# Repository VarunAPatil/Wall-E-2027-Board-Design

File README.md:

# Wall-E SRA Board · 2026–27

**A KiCad hardware platform for the Society of Robotics and Automation (SRA), VJTI.**

The SRA board brings the control, sensing, display, power, and motor interfaces for a small mobile robot onto one development board. This repository contains the main SRA board design, its companion Line Sensor Array (LSA), local KiCad libraries, 3D models, and fabrication exports.

---

## At a glance

| Area | Design |
| --- | --- |
| Main controller | ESP32-S3-WROOM-1 module |
| Input and power | 12 V input, TPS54302 step-down stage, 5 V rail, AMS1117-3.3 V regulator |
| Motor control | TB6612FNG dual H-bridge and two motor outputs |
| Robot sensing | 10-pin FFC connection for the LSA; MPU-6050 connection |
| User interface | OLED connection, MAX7219-driven 8×8 LED matrix, buttons and status signals |
| Host connection | USB-C USB 2.0 interface for development and programming |
| Design tools | KiCad schematic, PCB, project and local symbol/footprint libraries |

> **Design status:** This repository contains design files and exported fabrication data. Their presence does not by itself confirm electrical validation, manufacturing quality, or tested board behavior. Check the current schematic, PCB, and fabrication outputs before ordering or assembling hardware.

## System overview

```mermaid
flowchart LR
    P[12 V input] --> PR[Input protection and switching]
    PR --> B[TPS54302 buck stage]
    B --> V5[5 V rail]
    V5 --> L[AMS1117-3.3 V regulator]
    V5 --> M[TB6612FNG motor driver]
    L --> C[ESP32-S3]
    C <--> U[USB-C USB 2.0]
    C <--> D[MAX7219 LED matrix]
    C <--> O[OLED]
    C <--> I[MPU-6050]
    C <--> A[10-pin FFC to LSA]
    M --> W[Left and right motor outputs]
```

The power design separates the motor supply from the regulated logic rails. The schematic shows a TPS54302 switching regulator for the 5 V rail and an AMS1117-3.3 for 3.3 V logic. Resettable PTC fuses are used in the design; the schematic lists 3 A and 1 A parts. These values describe the selected components, not a verified continuous-current rating for a completed board.

The main controller connects to the motor driver and the board peripherals. The TB6612FNG provides two H-bridge channels for two DC motor outputs. The MAX7219 handles the LED matrix interface, reducing the number of controller signals needed for the display. The OLED and MPU-6050 connect as board peripherals, and the companion LSA connects over the 10-pin FFC interface.

## Board features

### SRA controller board

- **ESP32-S3 control:** Wi-Fi/Bluetooth-capable MCU module and GPIO-based control for the robot and its peripherals.
- **USB-C interface:** USB 2.0 data connection to the controller for development and programming.
- **12 V power path:** board input with switching and protection circuitry, followed by regulated 5 V and 3.3 V rails.
- **Dual motor driver:** TB6612FNG H-bridge with separate control signals and two motor connectors.
- **Line sensing:** 10-position, 1.0 mm pitch FFC connector to the companion LSA board.
- **Motion sensing:** connection for an MPU-6050 inertial measurement module.
- **Display and feedback:** OLED connection and an 8×8 LED matrix driven by a MAX7219.
- **Controls:** reset/boot buttons and board-level power control signals.

### Line Sensor Array (LSA)

The `lsa/` directory contains a separate KiCad project for the line sensor board. It connects to the SRA board through a 10-pin FFC cable. Its schematic includes five analog sensor outputs labelled `LSA_A0` through `LSA_A4`; use the schematic and board pin labels as the wiring reference when integrating it.

## Repository map

| Path | Contents |
| --- | --- |
| `sra_board.kicad_pro` | Main SRA KiCad project settings |
| `sra_board.kicad_sch` | Main board schematic |
| `sra_board.kicad_pcb` | Main board PCB layout |
| `sra_board.step` | 3D STEP export of the main board assembly |
| `lsa/lsa.kicad_pro` | LSA KiCad project settings |
| `lsa/lsa.kicad_sch` | LSA schematic |
| `lsa/lsa.kicad_pcb` | LSA PCB layout |
| `3D/` | Component STEP models used by the designs |
| `MAX7219/` | MAX7219 symbol, footprints, and supporting files |
| `footprints.pretty/` | Project-specific KiCad footprints |
| `fp-lib-table`, `sym-lib-table` | Project-local footprint and symbol library tables |
| `sra-board-final-iteration-2027/` | Gerber, drill, and job files for the SRA board |
| `lsa/LSA-Wall-E-2027/` | Gerber, drill, and job files for the LSA board |
| `assets/` | Reference board images from an earlier board snapshot; compare with the current PCB before relying on them |

## Open and work with the designs

1. Install KiCad and clone this repository with Git, or download the repository as a ZIP archive.
2. Open `sra_board.kicad_pro` in KiCad to work on the SRA board. Open `lsa/lsa.kicad_pro` for the LSA.
3. Keep the project files, library tables, local footprints, symbols, and 3D models together so KiCad can resolve the project-specific references.
4. Make schematic changes first, then update the PCB from the schematic in KiCad and review footprints, net assignments, clearances, and board geometry.
5. Re-export fabrication files from the reviewed PCB if it has changed. The checked-in Gerbers are snapshots and may not match later edits.

### Fabrication files

The two export directories contain copper, solder-mask, solder-paste, silkscreen, outline, drill, and Gerber job files. Use the matching directory for the board being fabricated. Before sending files to a manufacturer, confirm that the exports correspond to the intended revision and inspect the layer set, board outline, drill map, and fabrication notes in a Gerber viewer.

The `.step` files are for mechanical and enclosure review. They are not substitutes for the KiCad source files or fabrication exports.

## Power and battery notes

The board is designed around a 12 V input for the motor and board power path. If using a three-cell lithium-ion battery pack, use a correctly rated external 3S battery-management system (BMS) and charger. The BMS is not the board’s battery charger. Confirm the voltage range, polarity, connector pinout, fuse suitability, motor current, regulator thermal limits, and wiring before powering a completed assembly.

## Project context and contributors

The SRA board is used in SRA VJTI robotics work, including the [Wall-E](https://github.com/SRA-VJTI/Wall-E) and [MARIO](https://github.com/SRA-VJTI/MARIO) projects. The board is designed in KiCad.

- [Varun Patil](https://github.com/VarunAPatil) — Designer
- [Omkar Nanajkar](https://github.com/nomkar24) — Designer

## License

There is no `LICENSE` file in this repository at present. Check with the project maintainers before reusing or redistributing the hardware design.

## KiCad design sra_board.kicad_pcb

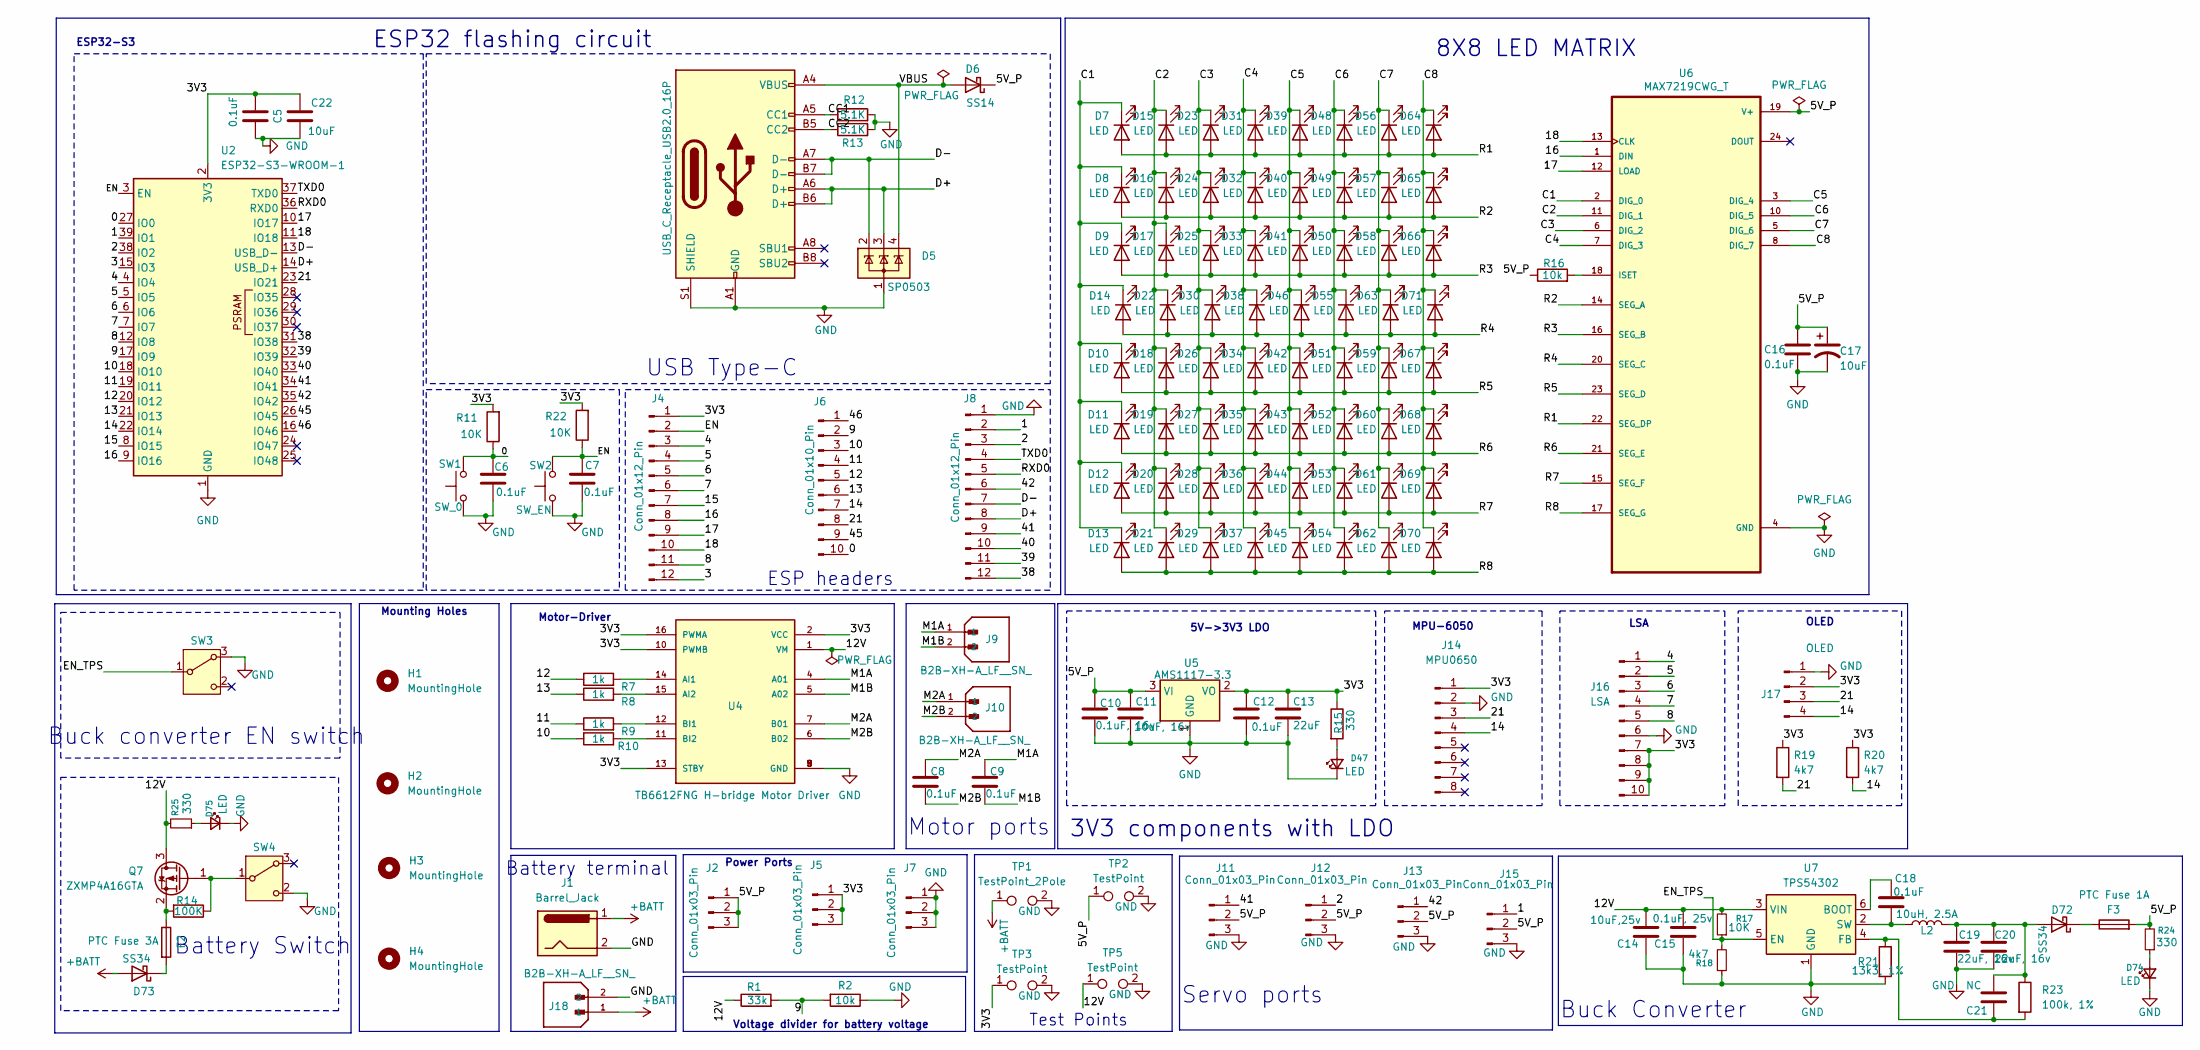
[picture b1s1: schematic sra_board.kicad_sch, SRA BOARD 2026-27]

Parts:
C5, C6, C7, C12, C16, C18: 0.1uF; C_0805_2012Metric
C8, C9: 0.1uF; C_1206_3216Metric
C10: 0.1uF, 16v; C_0805_2012Metric
C11: 10uF, 16v; C_0805_2012Metric
C13: 22uF; C_0805_2012Metric
C14: 10uF,25v; C_1206_3216Metric
C15: 0.1uF, 25v; C_1206_3216Metric
C17, C22: 10uF; C_0805_2012Metric
C19, C20: 22uF, 16v; C_1206_3216Metric
C21: NC; C_0805_2012Metric
D5: SP0503; SOT-143
D6: SS14; D_SMA
D7, D8, D9, D10, D11, D12, D13, D14, D15, D16, D17, D18, D19, D20, D21, D22, D23, D24, D25, D26, D27, D28, D29, D30, D31, D32, D33, D34, D35, D36, D37, D38, D39, D40, D41, D42, D43, D44, D45, D46, D47, D48, D49, D50, D51, D52, D53, D54, D55, D56, D57, D58, D59, D60, D61, D62, D63, D64, D65, D66, D67, D68, D69, D70, D71, D74, D75: LED; LED_0805_2012Metric
D72, D73: SS34; D_SMB
F2: PTC Fuse 3A; Fuse_2920_7451Metric
F3: PTC Fuse 1A; Fuse_1812_4532Metric
H1, H2, H3, H4: MountingHole; MountingHole_3.2mm_M3_DIN965_Pad_TopOnly
J1: Barrel_Jack; BarrelJack_Wuerth_6941xx301002
J2, J5, J7, J11, J12, J13, J15: Conn_01x03_Pin; PinHeader_1x03_P2.54mm_Vertical
J3: USB_C_Receptacle_USB2.0_16P; USB_C_Receptacle_GCT_USB4110
J4, J8: Conn_01x12_Pin; PinHeader_1x12_P2.54mm_Vertical
J6: Conn_01x10_Pin; PinHeader_1x10_P2.54mm_Vertical
J9, J10, J18: B2B-XH-A_LF__SN_; JST_EH_B2B-EH-A_1x02_P2.50mm_Vertical; PARTREV N/A
J14: MPU0650; PinSocket_1x08_P2.54mm_Vertical
J16: LSA; JUSHUO_AFA07-S10FCA-00_1x10-1MP_P1.0mm_Horizontal
J17: OLED; PinSocket_1x04_P2.54mm_Vertical
L2: 10uH, 2.5A; L_Sunlord_MWSA0603S
Q7: ZXMP4A16GTA; SOT-223
R1: 33k; R_0805_2012Metric
R2, R16: 10k; R_0805_2012Metric
R7, R8, R9, R10: 1k; R_0805_2012Metric
R11, R17, R22: 10K; R_0805_2012Metric
R12, R13: 5.1K; R_0805_2012Metric
R14: 100K; R_0805_2012Metric
R15, R24, R25: 330; R_0805_2012Metric
R18, R19, R20: 4k7; R_0805_2012Metric
R21: 13k3, 1%; R_0805_2012Metric
R23: 100k, 1%; R_0805_2012Metric
SW1: SW_0; SW_Push_SPST_NO_Alps_SKRK
SW2: SW_EN; SW_Push_SPST_NO_Alps_SKRK
SW3, SW4: SMD Slide switch; SW_SPDT_Shouhan_MSK12C02
TP1: TestPoint_2Pole; test_point
TP2, TP3, TP5: TestPoint; test_point
U2: ESP32-S3-WROOM-1
U4: TB6612FNG H-bridge Motor Driver; MODULE_ROB-14450
U5: AMS1117-3.3; SOT-223-3_TabPin2
U6: MAX7219CWG_T; SOIC24
U7: TPS54302; SOT-23-6

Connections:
+BATT: D73.2 (A), J1.1, J18.1, TP1.1 (1_1)
/0: C6.2, J6.10, R11.1, SW1.2, U2.27 (IO0)
/1: J8.2, J15.1, U2.39 (IO1)
/2: J8.3, J12.1, U2.38 (IO2)
/3: J4.12, U2.15 (IO3)
/3V3: C5.2, C12.1, C13.1, C22.1, J4.1, J5.1, J5.2, J5.3, J14.1, J16.7, J16.8, J16.9, J16.10, J17.2, R11.2, R15.1, R19.1, R20.1, R22.2, TP3.1 (1_1), U2.2 (3V3), U4.2 (VCC), U4.10 (PWMB), U4.13 (STBY), U4.16 (PWMA), U5.2 (VO)
/4: J4.3, J16.1, U2.4 (IO4)
/5: J4.4, J16.2, U2.5 (IO5)
/5V_P: C10.1, C11.1, C16.1, C17.1, D6.1 (K), F3.2, J2.1, J2.2, J2.3, J11.2, J12.2, J13.2, J15.2, R16.1, R24.2, TP2.1 (1_1), U5.3 (VI), U6.19 (V+)
/6: J4.5, J16.3, U2.6 (IO6)
/7: J4.6, J16.4, U2.7 (IO7)
/8: J4.11, J16.5, U2.12 (IO8)
/9: J6.2, R1.2, R2.2, U2.17 (IO9); also elsewhere on the board
/10: J6.3, R10.1, U2.18 (IO10)
/11: J6.4, R9.1, U2.19 (IO11)
/12: J6.5, R7.1, U2.20 (IO12)
/12V: C14.1, C15.1, Q7.3 (D), R1.1, R17.2, R25.2, TP5.1 (1_1), U4.1 (VM), U7.3 (VIN); also elsewhere on the board
/13: J6.6, R8.1, U2.21 (IO13)
/14: J6.7, J14.4, J17.4, R20.2, U2.22 (IO14)
/15: J4.7, U2.8 (IO15)
/16: J4.8, U2.9 (IO16), U6.1 (DIN)
/17: J4.9, U2.10 (IO17), U6.12 (LOAD)
/18: J4.10, U2.11 (IO18), U6.13 (CLK)
/21: J6.8, J14.3, J17.3, R19.2, U2.23 (IO21)
/38: J8.12, U2.31 (IO38)
/39: J8.11, U2.32 (IO39)
/40: J8.10, U2.33 (IO40)
/41: J8.9, J11.1, U2.34 (IO41)
/42: J8.6, J13.1, U2.35 (IO42)
/45: J6.9, U2.26 (IO45)
/46: J6.1, U2.16 (IO46)
/C1: D7.1 (K), D8.1 (K), D9.1 (K), D10.1 (K), D11.1 (K), D12.1 (K), D13.1 (K), D14.1 (K), U6.2 (DIG_0)
/C2: D15.1 (K), D16.1 (K), D17.1 (K), D18.1 (K), D19.1 (K), D20.1 (K), D21.1 (K), D22.1 (K), U6.11 (DIG_1)
/C3: D23.1 (K), D24.1 (K), D25.1 (K), D26.1 (K), D27.1 (K), D28.1 (K), D29.1 (K), D30.1 (K), U6.6 (DIG_2)
/C4: D31.1 (K), D32.1 (K), D33.1 (K), D34.1 (K), D35.1 (K), D36.1 (K), D37.1 (K), D38.1 (K), U6.7 (DIG_3)
/C5: D39.1 (K), D40.1 (K), D41.1 (K), D42.1 (K), D43.1 (K), D44.1 (K), D45.1 (K), D46.1 (K), U6.3 (DIG_4)
/C6: D48.1 (K), D49.1 (K), D50.1 (K), D51.1 (K), D52.1 (K), D53.1 (K), D54.1 (K), D55.1 (K), U6.10 (DIG_5)
/C7: D56.1 (K), D57.1 (K), D58.1 (K), D59.1 (K), D60.1 (K), D61.1 (K), D62.1 (K), D63.1 (K), U6.5 (DIG_6)
/C8: D64.1 (K), D65.1 (K), D66.1 (K), D67.1 (K), D68.1 (K), D69.1 (K), D70.1 (K), D71.1 (K), U6.8 (DIG_7)
/CC1: J3.A5 (CC1), R12.1; also elsewhere on the board
/CC2: J3.B5 (CC2), R13.1; also elsewhere on the board
/D+: D5.3 (K), J3.A6 (D+), J3.B6 (D+), J8.8, U2.14 (USB_D+); also elsewhere on the board
/D-: D5.2 (K), J3.A7 (D-), J3.B7 (D-), J8.7, U2.13 (USB_D-); also elsewhere on the board
/EN: C7.2, J4.2, R22.1, SW2.2, U2.3 (EN)
/EN_TPS: R17.1, R18.2, SW3.1 (B), U7.5 (EN)
/M1A: C9.1, J9.1, U4.4 (A01)
/M1B: C9.2, J9.2, U4.5 (A02)
/M2A: C8.1, J10.1, U4.7 (B01)
/M2B: C8.2, J10.2, U4.6 (B02)
/R1: D7.2 (A), D15.2 (A), D23.2 (A), D31.2 (A), D39.2 (A), D48.2 (A), D56.2 (A), D64.2 (A), U6.22 (SEG_DP)
/R2: D8.2 (A), D16.2 (A), D24.2 (A), D32.2 (A), D40.2 (A), D49.2 (A), D57.2 (A), D65.2 (A), U6.14 (SEG_A)
/R3: D9.2 (A), D17.2 (A), D25.2 (A), D33.2 (A), D41.2 (A), D50.2 (A), D58.2 (A), D66.2 (A), U6.16 (SEG_B)
/R4: D14.2 (A), D22.2 (A), D30.2 (A), D38.2 (A), D46.2 (A), D55.2 (A), D63.2 (A), D71.2 (A), U6.20 (SEG_C)
/R5: D10.2 (A), D18.2 (A), D26.2 (A), D34.2 (A), D42.2 (A), D51.2 (A), D59.2 (A), D67.2 (A), U6.23 (SEG_D)
/R6: D11.2 (A), D19.2 (A), D27.2 (A), D35.2 (A), D43.2 (A), D52.2 (A), D60.2 (A), D68.2 (A), U6.21 (SEG_E)
/R7: D12.2 (A), D20.2 (A), D28.2 (A), D36.2 (A), D44.2 (A), D53.2 (A), D61.2 (A), D69.2 (A), U6.15 (SEG_F)
/R8: D13.2 (A), D21.2 (A), D29.2 (A), D37.2 (A), D45.2 (A), D54.2 (A), D62.2 (A), D70.2 (A), U6.17 (SEG_G)
/RXD0: J8.5, U2.36 (RXD0)
/TXD0: J8.4, U2.37 (TXD0)
/VBUS: D5.4 (K), D6.2 (A), J3.A4 (VBUS), J3.A9 (VBUS), J3.B4 (VBUS), J3.B9 (VBUS); also elsewhere on the board
GND: C5.1, C6.1, C7.1, C10.2, C11.2, C12.2, C13.2, C14.2, C15.2, C16.2, C17.2, C19.2, C20.2, C22.2, D5.1 (A), D47.1 (K), D74.1 (K), D75.1 (K), J1.2, J3.A1 (GND), J3.A12 (GND), J3.B1 (GND), J3.B12 (GND), J3.S1 (SHIELD), J7.1, J7.2, J7.3, J8.1, J11.3, J12.3, J13.3, J14.2, J15.3, J16.6, J17.1, J18.2, R2.1, R12.2, R13.2, R18.1, R21.2, SW1.1 (1_1), SW2.1, SW3.3 (A), SW4.2 (C), TP1.2, TP2.2, TP3.2, TP5.2, U2.1 (GND), U2.40 (GND), U2.41 (GND), U4.3 (GND), U4.8 (GND), U4.9 (GND), U5.1 (GND), U6.4 (GND), U6.9 (GND), U7.1 (GND); also elsewhere on the board
unnamed: D47.2 (A), R15.2
unnamed: C19.1, C20.1, C21.1, D72.2 (A), L2.2, R23.1
unnamed: D72.1 (K), F3.1
unnamed: D73.1 (K), F2.2
unnamed: D74.2 (A), R24.1
unnamed: D75.2 (A), R25.1
unnamed: Q7.1 (G), R14.1, SW4.1 (B)
unnamed: F2.1, Q7.2 (S), R14.2
unnamed: R7.2, U4.14 (AI1)
unnamed: R8.2, U4.15 (AI2)
unnamed: R9.2, U4.12 (BI1)
unnamed: R10.2, U4.11 (BI2)
unnamed: R16.2, U6.18 (ISET)
unnamed: C18.1, U7.6 (BOOT)
unnamed: C21.2, R21.1, R23.2, U7.4 (FB)
unnamed: C18.2, L2.1, U7.2 (SW)

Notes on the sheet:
ESP32 flashing circuit
Power Ports
Motor-Driver
5V->3V3 LDO
ESP32-S3
Mounting Holes
Buck Converter
8X8 LED MATRIX
ESP headers
MPU-6050
Battery terminal
Voltage divider for battery voltage
LSA
OLED
3V3 components with LDO
Test Points
Battery Switch
USB Type-C
Servo ports
Buck converter EN switch
Motor ports

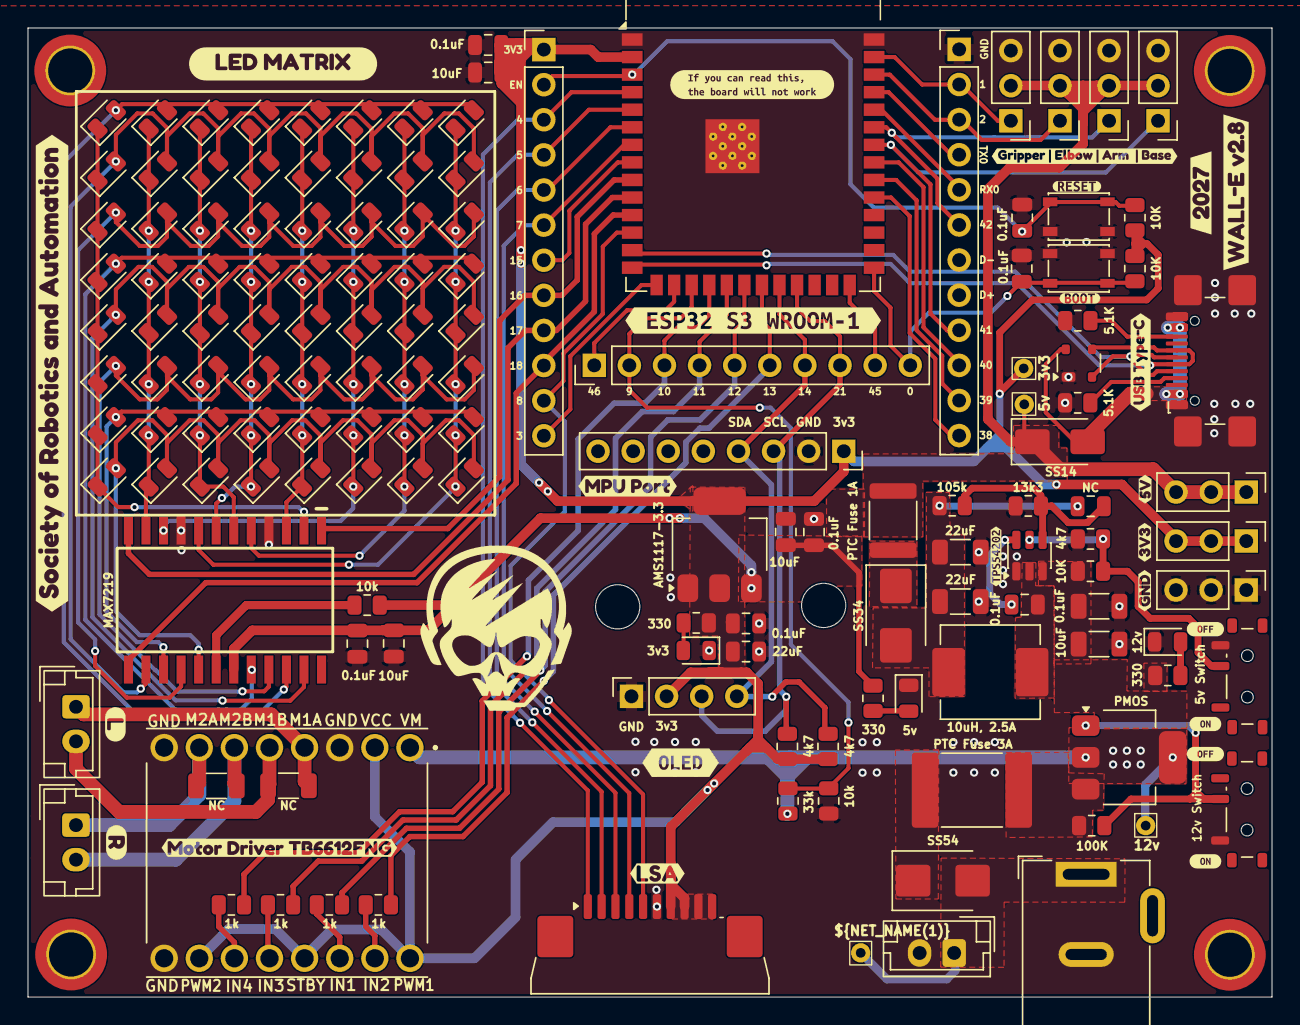
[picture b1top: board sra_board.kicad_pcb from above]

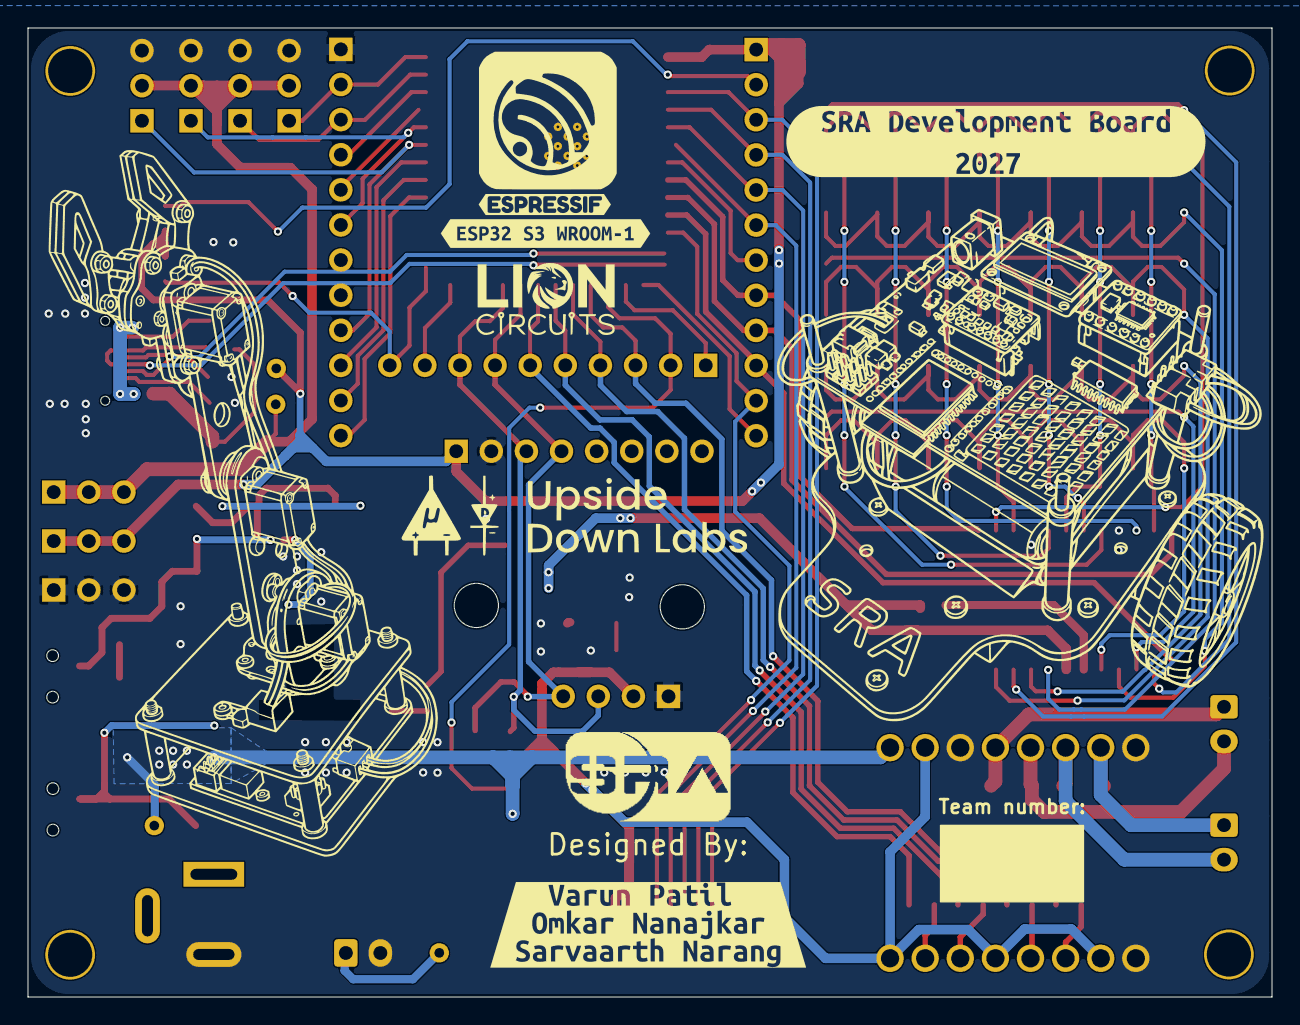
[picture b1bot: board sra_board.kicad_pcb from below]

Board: 2 copper layers, 90.0 x 70.1 mm, 179 parts (4 on the bottom side), 77 nets.

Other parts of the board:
10k: 10k; R_0805_2012Metric
33k3: 33k; R_0805_2012Metric
H5, H6: MountingHole; MountingHole_3.2mm_M3
J20: USB_C_Receptacle_USB2.0_16P; USB_C_Receptacle_GCT_USB4110
kibuzzard-6A8B3292: G***; kibuzzard-6A8B3292
kibuzzard-6A95D08E: G***; kibuzzard-6A95D08E
kibuzzard-6A955F10: G***; kibuzzard-6A955F10
kibuzzard-6A9563B5: G***; kibuzzard-6A9563B5
kibuzzard-6AB2B412, kibuzzard-6AB2B412#2: G***; kibuzzard-6AB2B412
kibuzzard-6AB2B440, kibuzzard-6AB2B440#2: G***; kibuzzard-6AB2B440
kibuzzard-6ABFEC95: G***; kibuzzard-6ABFEC95
kibuzzard-6ABFECB0: G***; kibuzzard-6ABFECB0
kibuzzard-6AC0B409: G***; kibuzzard-6AC0B409
kibuzzard-6AC3A33F: G***; kibuzzard-6AC3A33F
kibuzzard-6AC3A571: G***; kibuzzard-6AC3A571
kibuzzard-6AC39C0C: G***; kibuzzard-6AC39C0C
kibuzzard-6AC39C9E: G***; kibuzzard-6AC39C9E
kibuzzard-6AC39C35: G***; kibuzzard-6AC39C35
kibuzzard-6AC39D95: G***; kibuzzard-6AC39D95
kibuzzard-68E7F907: G***; kibuzzard-68E7F907
kibuzzard-658F2C3C: G***; kibuzzard-658F2C3C
kibuzzard-668D4F81: G***; kibuzzard-668D4F81
kibuzzard-668FE423: G***; kibuzzard-668FE423
kibuzzard-6774F4AA: G***; kibuzzard-6774F4AA
kibuzzard-6774F4AE: G***; kibuzzard-6774F4AE
kibuzzard-67704CCE: G***; kibuzzard-67704CCE
kibuzzard-67704CDF: G***; kibuzzard-67704CDF
kibuzzard-67704CF4: G***; kibuzzard-67704CF4
kibuzzard-66921043: G***; kibuzzard-66921043
kibuzzard-66923428: G***; kibuzzard-66923428

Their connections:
/9: 10k.2, 33k3.2; also elsewhere on the board
/12V: 33k3.1; also elsewhere on the board
/CC1: J20.A5 (CC1); also elsewhere on the board
/CC2: J20.B5 (CC2); also elsewhere on the board
/D+: J20.A6 (D+), J20.B6 (D+); also elsewhere on the board
/D-: J20.A7 (D-), J20.B7 (D-); also elsewhere on the board
/VBUS: J20.A4 (VBUS), J20.A9 (VBUS), J20.B4 (VBUS), J20.B9 (VBUS); also elsewhere on the board
GND: 10k.1, J20.A1 (GND), J20.A12 (GND), J20.B1 (GND), J20.B12 (GND), J20.S1 (SHIELD); also elsewhere on the board

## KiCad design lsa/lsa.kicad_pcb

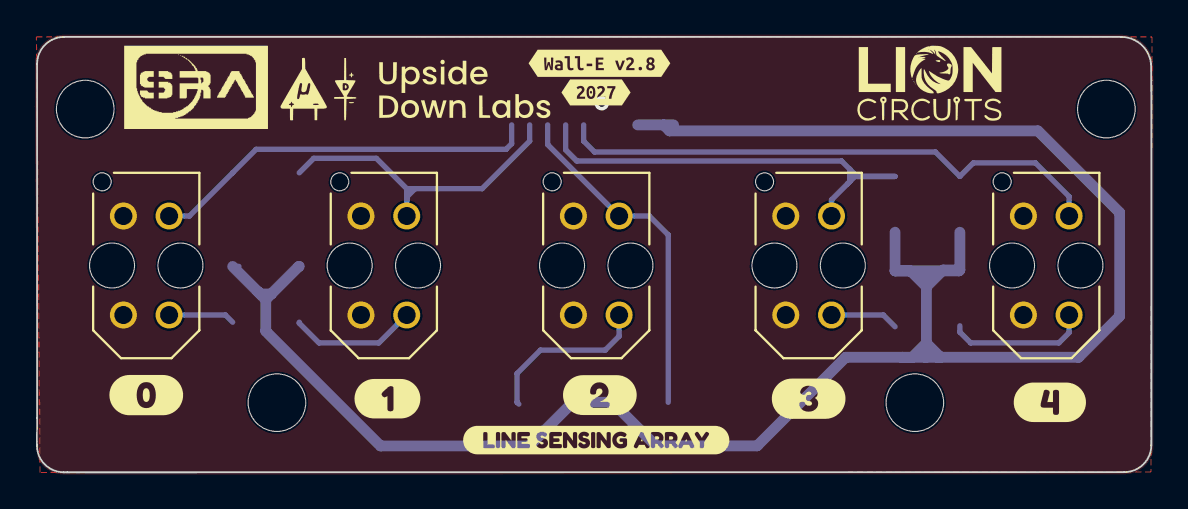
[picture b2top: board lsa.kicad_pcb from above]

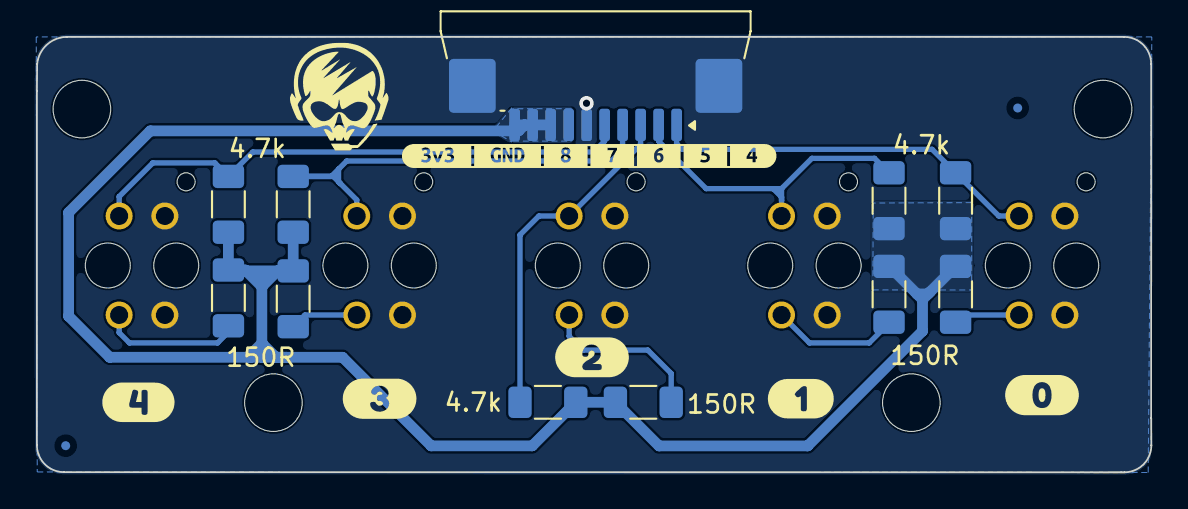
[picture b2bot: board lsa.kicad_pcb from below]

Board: 2 copper layers, 61.9 x 24.2 mm, 30 parts (17 on the bottom side), 12 nets.

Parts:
J2: Conn_01x10_Pin; JUSHUO_AFA07-S10FCA-00_1x10-1MP_P1.0mm_Horizontal
R1, R3, R5, R7, R9: 4.7k; R_1206_3216Metric_Pad1.30x1.75mm_HandSolder
R2, R4, R6, R8, R10: 150R; R_1206_3216Metric_Pad1.30x1.75mm_HandSolder
U1, U2, U3, U4, U5: TCRT5000; OPTO_TCRT5000
kibuzzard-6A70DDC1: G***; kibuzzard-6A70DDC1
kibuzzard-6A70DDE3: G***; kibuzzard-6A70DDE3
kibuzzard-6AC3C74E: G***; kibuzzard-6AC3C74E
kibuzzard-672CF9E4: G***; kibuzzard-672CF9E4
kibuzzard-63708D58, kibuzzard-63708D58#2: G***; kibuzzard-63708D58
kibuzzard-63708D75, kibuzzard-63708D75#2: G***; kibuzzard-63708D75
kibuzzard-63708D85, kibuzzard-63708D85#2: G***; kibuzzard-63708D85
kibuzzard-63708DAF, kibuzzard-63708DAF#2: G***; kibuzzard-63708DAF
kibuzzard-63708DBF, kibuzzard-63708DBF#2: G***; kibuzzard-63708DBF

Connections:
+3V3: J2.7, J2.8, J2.9, J2.10, R1.1, R2.2, R3.1, R4.2, R5.1, R6.2, R7.1, R8.2, R9.1, R10.2
/A0_36: J2.5, R1.2, U1.COLL
/A1_39: J2.4, R3.2, U2.COLL
/A2_34: J2.3, R5.2, U3.COLL
/A3_35: J2.2, R7.2, U4.COLL
/A4_32: J2.1, R9.2, U5.COLL
GND: J2.6, J2.MP, U1.CATH, U1.E, U2.CATH, U2.E, U3.CATH, U3.E, U4.CATH, U4.E, U5.CATH, U5.E
unnamed: R2.1, U1.A
unnamed: R4.1, U2.A
unnamed: R6.1, U3.A
unnamed: R8.1, U4.A
unnamed: R10.1, U5.A

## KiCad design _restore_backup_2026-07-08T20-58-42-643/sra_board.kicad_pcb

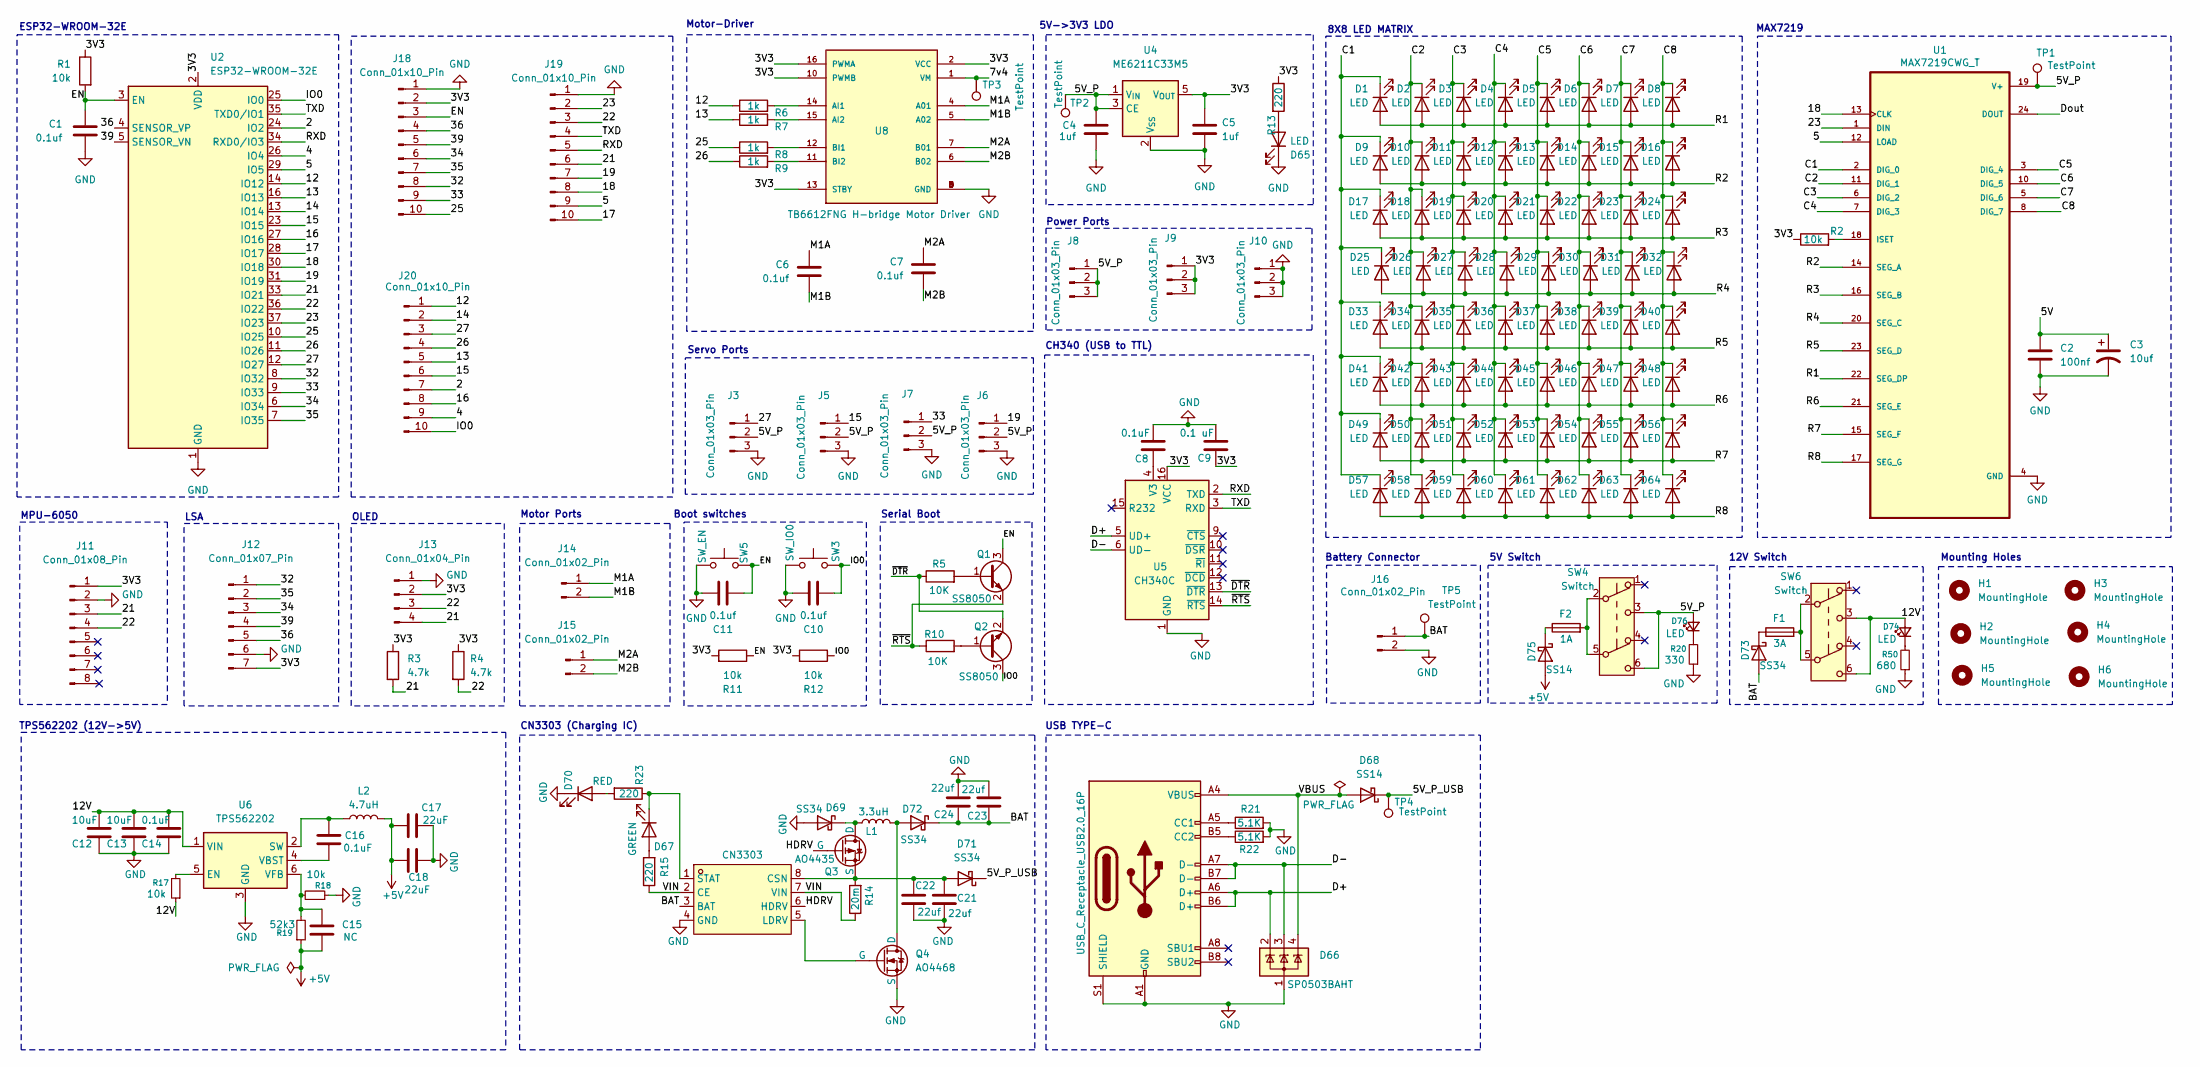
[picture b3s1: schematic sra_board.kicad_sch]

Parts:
C1, C6, C7, C10, C11: 0.1uf; C_0603_1608Metric
C2: 100nf; C_0603_1608Metric
C3: 10uf; C_0603_1608Metric
C4, C5: 1uf; C_0603_1608Metric
C8, C14, C16: 0.1uF; C_0603_1608Metric
C9: 0.1 uF; C_0603_1608Metric
C12, C13: 10uF; C_0603_1608Metric
C15: NC; C_0603_1608Metric
C17, C18: 22uF; C_0603_1608Metric
C21, C22, C23, C24: 22uf; C_0603_1608Metric
D1, D2, D3, D4, D5, D6, D7, D8, D9, D10, D11, D12, D13, D14, D15, D16, D17, D18, D19, D20, D21, D22, D23, D24, D25, D26, D27, D28, D29, D30, D31, D32, D33, D34, D35, D36, D37, D38, D39, D40, D41, D42, D43, D44, D45, D46, D47, D48, D49, D50, D51, D52, D53, D54, D55, D56, D57, D58, D59, D60, D61, D62, D63, D64, D65: LED; LED_0603_1608Metric
D66: SP0503BAHT; SOT-143
D67: GREEN; LED_0603_1608Metric
D68, D75: SS14; D_SMA
D69, D71, D72: SS34; D_SMA
D70: RED; LED_0603_1608Metric
D73: SS34; D_SMB
D74, D76: LED; LED_0603_1608Metric_Pad1.05x0.95mm_HandSolder
F1: 3A; Fuse_Littelfuse-LVR100
F2: 1A; Fuse_Littelfuse-LVR100
H1, H2, H3, H4, H5, H6: MountingHole; MountingHole_3.2mm_M3
J3, J5, J6, J7, J8, J9, J10: Conn_01x03_Pin; PinHeader_1x03_P2.54mm_Vertical
J11: Conn_01x08_Pin; PinSocket_1x08_P2.54mm_Vertical
J12: Conn_01x07_Pin; JST_EH_S7B-EH_1x07_P2.50mm_Horizontal
J13: Conn_01x04_Pin; PinHeader_1x04_P2.54mm_Vertical
J14, J15: Conn_01x02_Pin; JST_EH_B2B-EH-A_1x02_P2.50mm_Vertical
J16: Conn_01x02_Pin; JST_EH_S2B-EH_1x02_P2.50mm_Horizontal
J17: USB_C_Receptacle_USB2.0_16P; USB_C_Receptacle_GCT_USB4105-xx-A_16P_TopMnt_Horizontal
J18, J19, J20: Conn_01x10_Pin; PinHeader_1x10_P2.54mm_Vertical
L1: 3.3uH
L2: 4.7uH; L_Sunlord_MWSA0402S
Q1, Q2: SS8050; SOT-23
Q3: AO4435; SOT-23
Q4: AO4468; SOT-23
R1, R2, R11, R12, R17, R18: 10k; R_0603_1608Metric
R3, R4: 4.7k; R_0603_1608Metric
R5, R10: 10K; R_0603_1608Metric
R6, R7, R8, R9: 1k; R_0603_1608Metric
R13, R15, R23: 220; R_0603_1608Metric
R14: 20m; R_0603_1608Metric
R19: 52k3; R_0603_1608Metric
R20: 330; R_0603_1608Metric
R21, R22: 5.1K; R_0603_1608Metric
R50: 680; R_0603_1608Metric
SW3: SW_IO0; SW_Push_SPST_NO_Alps_SKRK
SW4, SW6: Switch; SW_Push_2P2T_Toggle_CK_PVA2OAH5xxxxxxV2
SW5: SW_EN; SW_Push_SPST_NO_Alps_SKRK
TP1, TP2, TP3, TP4, TP5: TestPoint; TestPoint_Pad_D1.0mm
U1: MAX7219CWG_T; SOIC127P1032X265-24N
U2: ESP32-WROOM-32E; ESP32-WROOM-32D
U4: ME6211C33M5; SOT-23-5
U5: CH340C; SOIC-16_3.9x9.9mm_P1.27mm
U6: TPS562202; SOT-563
U7: CN3303; SOP-8_L4.9-W3.9-P1.27-LS6.0-BL; MPN CN3302; LCSC Part C559039
U8: TB6612FNG H-bridge Motor Driver; MODULE_ROB-14450

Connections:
+5V: C15.2, C17.1, C18.1, D75.2 (A), L2.2, R19.1
/2: J20.7, U2.24 (IO2)
/3V3: C5.1, C9.1, J9.1, J9.2, J9.3, J11.1, J12.7, J13.2, J18.2, R1.1, R2.1, R3.1, R4.1, R11.2, R12.2, R13.1, U2.2 (VDD), U4.5 (V_{OUT}), U5.16 (VCC), U8.2 (VCC), U8.10 (PWMB), U8.13 (STBY), U8.16 (PWMA)
/4: J20.9, U2.26 (IO4)
/5: J19.9, U1.12 (LOAD), U2.29 (IO5)
/5V: C2.1, C3.1
/5V_P: C4.1, D76.2 (A), J3.2, J5.2, J6.2, J7.2, J8.1, J8.2, J8.3, SW4.3 (C), SW4.6 (C), TP1.1 (1_1), TP2.1 (1_1), U1.19 (V+), U4.1 (V_{IN}), U4.3 (CE)
/5V_P_USB: D68.1 (K), D71.1 (K), TP4.1 (1_1)
/7v4: TP3.1 (1_1), U8.1 (VM)
/12: J20.1, R6.1, U2.14 (IO12)
/12V: C12.1, C13.1, C14.1, D74.2 (A), R17.1, SW6.3 (C), SW6.6 (C), U6.1 (VIN)
/13: J20.5, R7.1, U2.16 (IO13)
/14: J20.2, U2.13 (IO14)
/15: J5.1, J20.6, U2.23 (IO15)
/16: J20.8, U2.27 (IO16)
/17: J19.10, U2.28 (IO17)
/18: J19.8, U1.13 (CLK), U2.30 (IO18)
/19: J6.1, J19.7, U2.31 (IO19)
/21: J11.3, J13.4, J19.6, R3.2, U2.33 (IO21)
/22: J11.4, J13.3, J19.3, R4.2, U2.36 (IO22)
/23: J19.2, U1.1 (DIN), U2.37 (IO23)
/25: J18.10, R8.1, U2.10 (IO25)
/26: J20.4, R9.1, U2.11 (IO26)
/27: J3.1, J20.3, U2.12 (IO27)
/32: J12.1, J18.8, U2.8 (IO32)
/33: J7.1, J18.9, U2.9 (IO33)
/34: J12.3, J18.6, U2.6 (IO34)
/35: J12.2, J18.7, U2.7 (IO35)
/36: J12.5, J18.4, U2.4 (SENSOR_VP)
/39: J12.4, J18.5, U2.5 (SENSOR_VN)
/BAT: C23.1, C24.1, D72.1 (K), D73.2 (A), J16.1, TP5.1 (1_1), U7.3 (BAT)
/C1: D1.1 (K), D9.1 (K), D17.1 (K), D25.1 (K), D33.1 (K), D41.1 (K), D49.1 (K), D57.1 (K), U1.2 (DIG_0)
/C2: D2.1 (K), D10.1 (K), D18.1 (K), D26.1 (K), D34.1 (K), D42.1 (K), D50.1 (K), D58.1 (K), U1.11 (DIG_1)
/C3: D3.1 (K), D11.1 (K), D19.1 (K), D27.1 (K), D35.1 (K), D43.1 (K), D51.1 (K), D59.1 (K), U1.6 (DIG_2)
/C4: D4.1 (K), D12.1 (K), D20.1 (K), D28.1 (K), D36.1 (K), D44.1 (K), D52.1 (K), D60.1 (K), U1.7 (DIG_3)
/C5: D5.1 (K), D13.1 (K), D21.1 (K), D29.1 (K), D37.1 (K), D45.1 (K), D53.1 (K), D61.1 (K), U1.3 (DIG_4)
/C6: D6.1 (K), D14.1 (K), D22.1 (K), D30.1 (K), D38.1 (K), D46.1 (K), D54.1 (K), D62.1 (K), U1.10 (DIG_5)
/C7: D7.1 (K), D15.1 (K), D23.1 (K), D31.1 (K), D39.1 (K), D47.1 (K), D55.1 (K), D63.1 (K), U1.5 (DIG_6)
/C8: D8.1 (K), D16.1 (K), D24.1 (K), D32.1 (K), D40.1 (K), D48.1 (K), D56.1 (K), D64.1 (K), U1.8 (DIG_7)
/D+: D66.2 (K), J17.A6 (D+), J17.B6 (D+), U5.5 (UD+)
/D-: D66.3 (K), J17.A7 (D-), J17.B7 (D-), U5.6 (UD-)
/EN: C1.1, C11.2, J18.3, Q1.3, R1.2, R11.1, SW5.2, U2.3 (EN)
/HDRV: Q3.2 (G), U7.6 (HDRV)
/IO0: C10.2, J20.10, Q2.3, R12.1, SW3.2, U2.25 (IO0)
/M1A: C6.1, J14.1, U8.4 (A01)
/M1B: C6.2, J14.2, U8.5 (A02)
/M2A: C7.1, J15.1, U8.7 (B01)
/M2B: C7.2, J15.2, U8.6 (B02)
/R1: D1.2 (A), D2.2 (A), D3.2 (A), D4.2 (A), D5.2 (A), D6.2 (A), D7.2 (A), D8.2 (A), U1.22 (SEG_DP)
/R2: D9.2 (A), D10.2 (A), D11.2 (A), D12.2 (A), D13.2 (A), D14.2 (A), D15.2 (A), D16.2 (A), U1.14 (SEG_A)
/R3: D17.2 (A), D18.2 (A), D19.2 (A), D20.2 (A), D21.2 (A), D22.2 (A), D23.2 (A), D24.2 (A), U1.16 (SEG_B)
/R4: D25.2 (A), D26.2 (A), D27.2 (A), D28.2 (A), D29.2 (A), D30.2 (A), D31.2 (A), D32.2 (A), U1.20 (SEG_C)
/R5: D33.2 (A), D34.2 (A), D35.2 (A), D36.2 (A), D37.2 (A), D38.2 (A), D39.2 (A), D40.2 (A), U1.23 (SEG_D)
/R6: D41.2 (A), D42.2 (A), D43.2 (A), D44.2 (A), D45.2 (A), D46.2 (A), D47.2 (A), D48.2 (A), U1.21 (SEG_E)
/R7: D49.2 (A), D50.2 (A), D51.2 (A), D52.2 (A), D53.2 (A), D54.2 (A), D55.2 (A), D56.2 (A), U1.15 (SEG_F)
/R8: D57.2 (A), D58.2 (A), D59.2 (A), D60.2 (A), D61.2 (A), D62.2 (A), D63.2 (A), D64.2 (A), U1.17 (SEG_G)
/RXD: J19.5, U2.34 (RXD0/IO3), U5.2 (TXD)
/TXD: J19.4, U2.35 (TXD0/IO1), U5.3 (RXD)
/VBUS: D66.4 (K), D68.2 (A), J17.A4 (VBUS), J17.A9 (VBUS), J17.B4 (VBUS), J17.B9 (VBUS)
/VIN: R14.1, R15.1, U7.2 (CE), U7.7 (VIN)
/~DTR: Q2.2, R5.1, U5.13 (~DTR)
/~RTS: Q1.2, R10.1, U5.14 (~RTS)
GND: C1.2, C2.2, C3.2, C4.2, C5.2, C8.2, C9.2, C10.1, C11.1, C12.2, C13.2, C14.2, C17.2, C18.2, C21.2, C22.2, C23.2, C24.2, D65.1 (K), D66.1 (A), D69.2 (A), D70.1 (K), J3.3, J5.3, J6.3, J7.3, J10.1, J10.2, J10.3, J11.2, J12.6, J13.1, J16.2, J17.A1 (GND), J17.A12 (GND), J17.B1 (GND), J17.B12 (GND), J17.S1 (SHIELD), J18.1, J19.1, Q4.3 (S), R18.1, R20.1, R21.2, R22.2, R50.1, SW3.1, SW5.1, U1.4 (GND), U1.9 (GND), U2.1 (GND), U2.15 (GND), U2.38 (GND), U2.39 (GND), U4.2 (V_{SS}), U5.1 (GND), U6.3 (GND), U7.4 (GND), U8.3 (GND), U8.8 (GND), U8.9 (GND)
unnamed: D65.2 (A), R13.2
unnamed: D67.2 (A), R15.2
unnamed: D67.1 (K), R23.1, U7.1 (STAT)
unnamed: D69.1 (K), L1.1, Q3.1 (D)
unnamed: D70.2 (A), R23.2
unnamed: C21.1, C22.1, D71.2 (A), Q3.3 (S), R14.2, U7.8 (CSN)
unnamed: D72.2 (A), L1.2, Q4.1 (D)
unnamed: D73.1 (K), F1.1
unnamed: D74.1 (K), R50.2
unnamed: D75.1 (K), F2.1
unnamed: D76.1 (K), R20.2
unnamed: F1.2, SW6.2 (B), SW6.5 (B)
unnamed: F2.2, SW4.2 (B), SW4.5 (B)
unnamed: J17.A5 (CC1), R21.1
unnamed: J17.B5 (CC2), R22.1
unnamed: Q1.1, R5.2
unnamed: Q2.1, R10.2
unnamed: Q4.2 (G), U7.5 (LDRV)
unnamed: R2.2, U1.18 (ISET)
unnamed: R6.2, U8.14 (AI1)
unnamed: R7.2, U8.15 (AI2)
unnamed: R8.2, U8.12 (BI1)
unnamed: R9.2, U8.11 (BI2)
unnamed: C8.1, U5.4 (V3)
unnamed: R17.2, U6.5 (EN)
unnamed: C16.1, L2.1, U6.2 (SW)
unnamed: C16.2, U6.4 (VBST)
unnamed: C15.1, R18.2, R19.2, U6.6 (VFB)

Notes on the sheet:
CH340 (USB to TTL)
Motor-Driver
5V Switch
ESP32-WROOM-32E
CN3303 (Charging IC)
Battery Connector
8X8 LED MATRIX
Mounting Holes
Serial Boot
12V Switch
Servo Ports
5V->3V3 LDO
Boot switches
LSA
Motor Ports
TPS562202 (12V->5V)
OLED
MPU-6050
USB TYPE-C
MAX7219
Power Ports

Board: 2 copper layers, 164 parts (0 on the bottom side), 83 nets, no tracks yet.

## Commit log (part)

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2026-05-24 added esp32, 8x8 LED Matrix with MAX
2026-05-29 Added Boot circuit and USB-to-TTL
2026-05-31 Adding power charging circuit for charging battery on seperate type-c
2026-05-31 Added OLED, Servo Ports, Power Ports, CH340, Boot circuit, Motor port
2026-05-31 Added rest of components
2026-06-03 Minor changes for formatting
2026-06-09 Using only one type c
2026-06-09 Making label correction
2026-06-10 Added CN3302 and TCP
2026-06-14 placed half components
2026-06-20 Adding dependencies for PCB
2026-06-20 rough placing of components
2026-06-20 Placement first draft along with 3D files
2026-06-21 Finishing the routing
2026-06-30 Added CN3303N circuit
2026-06-30 Fixed net labels
2026-06-30 fixed text labels
